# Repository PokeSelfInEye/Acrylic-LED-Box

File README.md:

# Acrylic-LED-Box
Files for acrylic lamp.

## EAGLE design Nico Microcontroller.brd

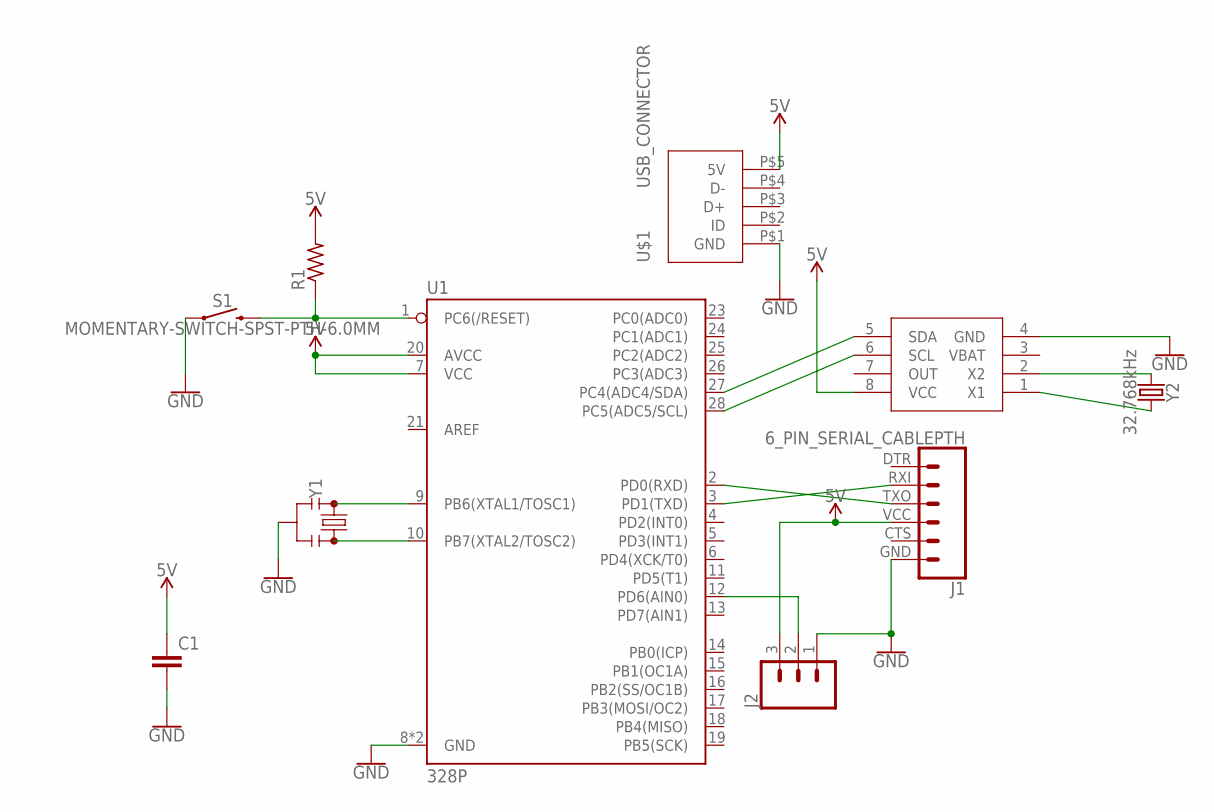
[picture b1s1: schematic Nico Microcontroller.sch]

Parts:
C1: C2.5/2; C2.5-2
J1: 6_PIN_SERIAL_CABLEPTH; FTDI_BASIC
J2: CONN_03; 1X03
R1: R-US_0204/5; 0204/5
S1: MOMENTARY-SWITCH-SPST-PTH-6.0MM; TACTILE_SWITCH_PTH_6.0MM
U1: 328P; DIP28
U$1: USB_CONNECTOR; USB-CONNECTOR
U$2: DS1307; DIP08
Y1: RESONATORPTH-7.6X3.8; RESONATOR-PTH-7.6X3.8
Y2: 32.768kHz; CRYSTAL-PTH-2X6-CYL

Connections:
5V: C1.1, J1.VCC (4), J2.3, R1.2, U1.7 (VCC), U1.20 (AVCC), U$1.P$5 (5V), U$2.8 (VCC)
GND: C1.2, J1.GND (6), J2.1, S1.1, U1.8 (GND), U1.22 (GND), U$1.P$1 (GND), U$2.4 (GND), Y1.2
unnamed: R1.1, S1.3 (2), U1.1 (PC6(/RESET))
unnamed: U1.9 (PB6(XTAL1/TOSC1)), Y1.1
unnamed: U1.10 (PB7(XTAL2/TOSC2)), Y1.3
unnamed: J1.RXI (2), U1.3 (PD1(TXD))
unnamed: J2.2, U1.12 (PD6(AIN0))
unnamed: J1.TXO (3), U1.2 (PD0(RXD))
unnamed: U1.27 (PC4(ADC4/SDA)), U$2.5 (SDA)
unnamed: U1.28 (PC5(ADC5/SCL)), U$2.6 (SCL)
unnamed: U$2.2 (X2), Y2.1
unnamed: U$2.1 (X1), Y2.2

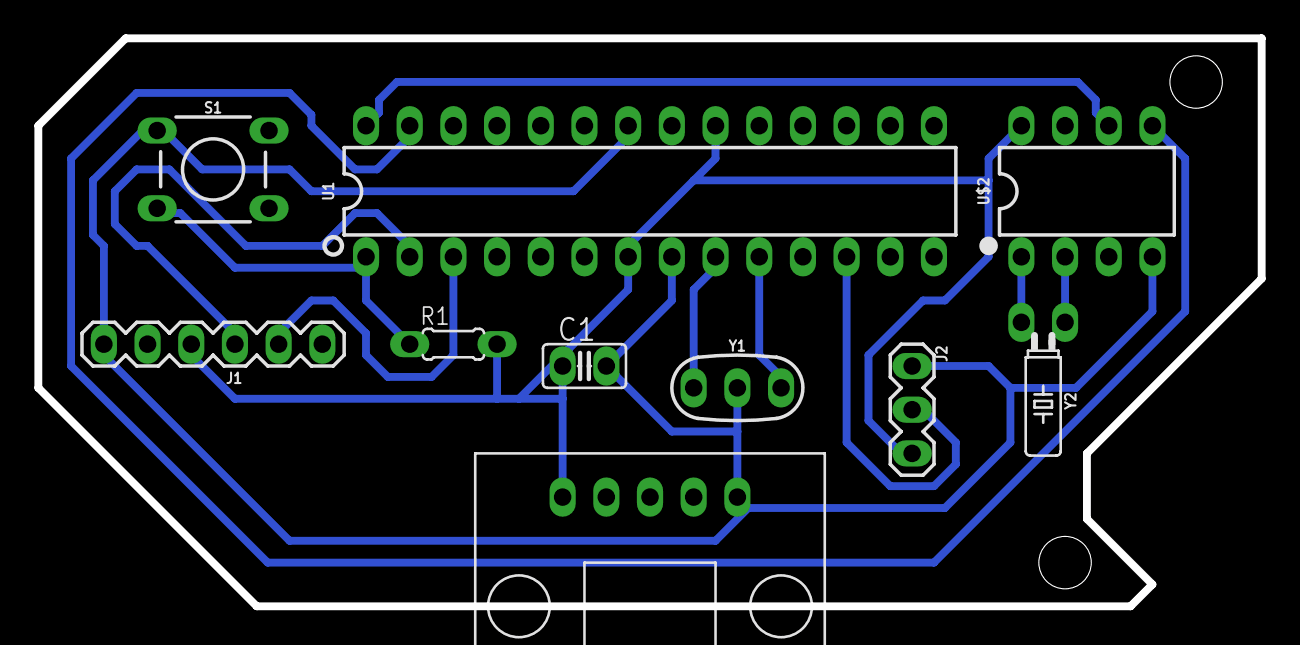
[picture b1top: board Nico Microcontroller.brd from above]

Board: 2 copper layers, 71.1 x 33.0 mm, 10 parts (0 on the bottom side), 12 nets.

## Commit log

2019-01-22 Added final code.
2019-02-13 Put all the things in here that I thought were.
2019-02-14 Added the project cost sheet.

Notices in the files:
parts and their libraries:
SparkFun-PowerSymbols: Licensing: Creative Commons ShareAlike 4.0 International - https://creativecommons.org/licenses/by-sa/4.0
